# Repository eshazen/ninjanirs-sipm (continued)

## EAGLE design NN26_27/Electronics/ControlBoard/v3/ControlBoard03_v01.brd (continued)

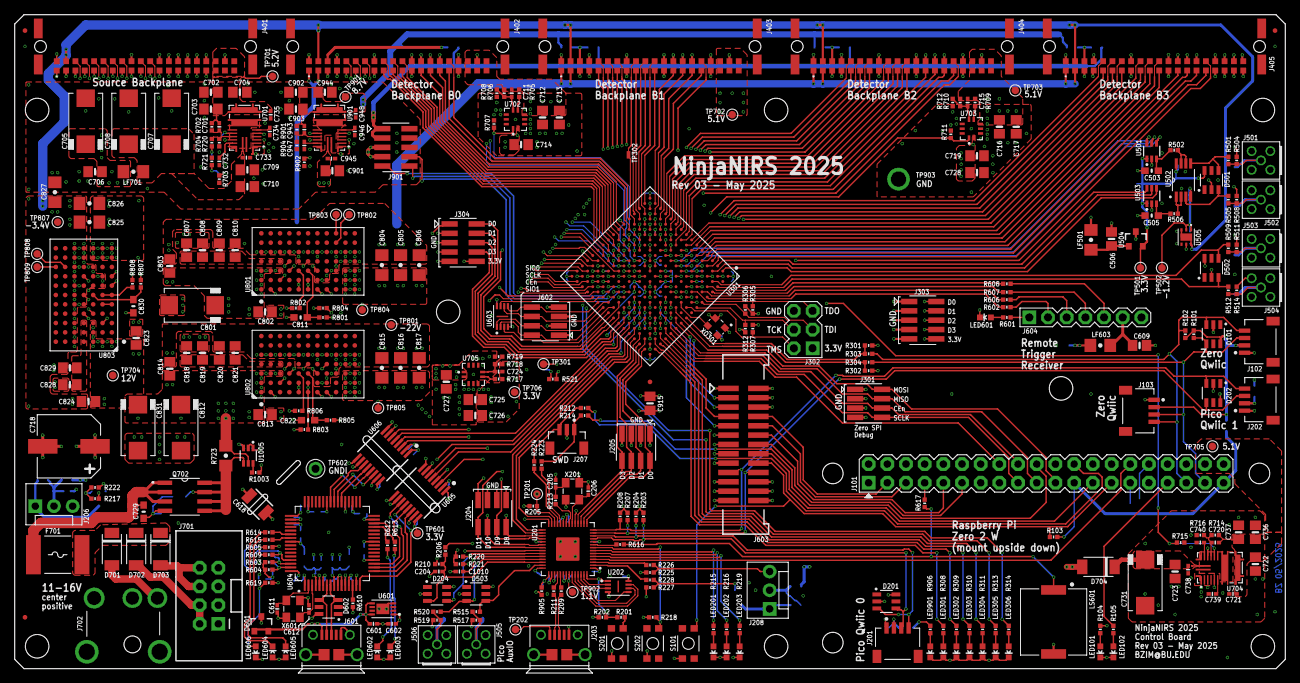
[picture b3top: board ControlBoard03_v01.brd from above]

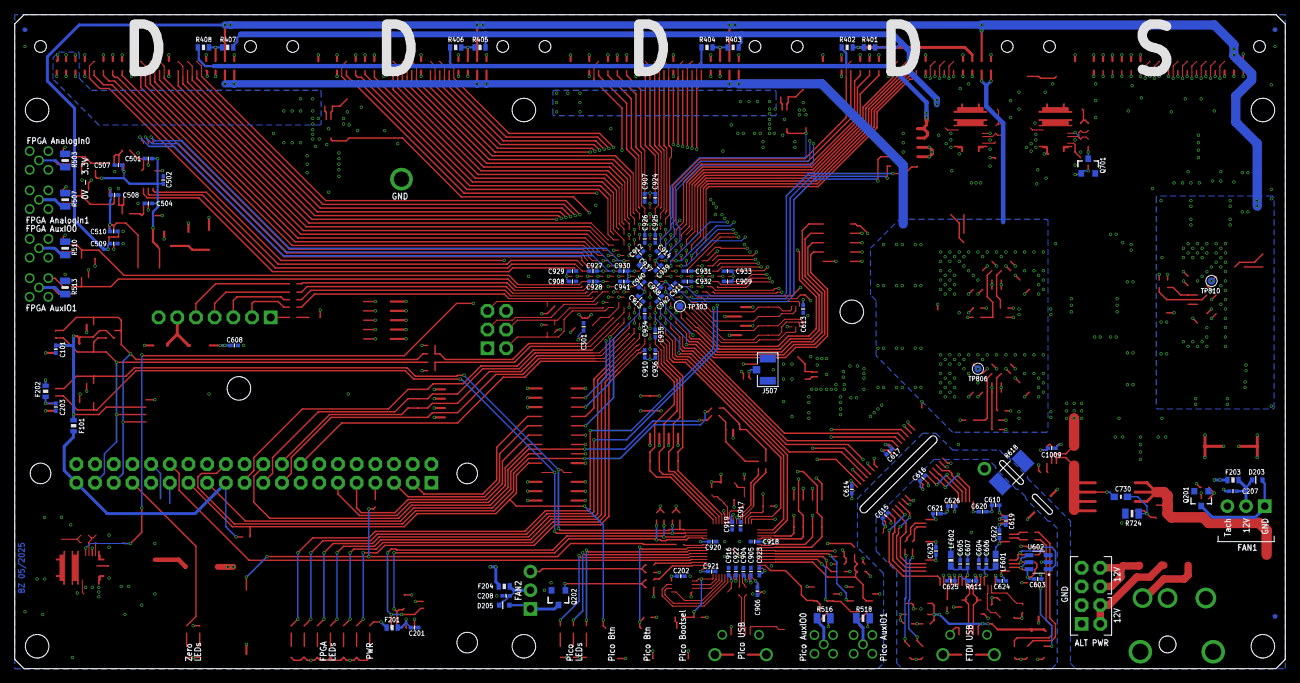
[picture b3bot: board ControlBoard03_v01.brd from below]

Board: 6 copper layers, 172.7 x 88.9 mm, 445 parts (111 on the bottom side), 379 nets.

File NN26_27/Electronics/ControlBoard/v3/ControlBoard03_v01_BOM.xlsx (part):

Designator | Value | Footprint | Populate | MPN | Manufacturer | MPN | Manufacturer
C1009 | 0.1u | 0402-CAP | 1 | GRM155R71H104KE14D | Murata
C101 | 0.1u | 0402-CAP | 1 | GRM155R71H104KE14D | Murata
C1010 | 0.1u | 0402-CAP | 1 | GRM155R71H104KE14D | Murata
C201 | 0.1u | 0402-CAP | 1 | GRM155R71H104KE14D | Murata
C202 | 0.1u | 0402-CAP | 1 | GRM155R71H104KE14D | Murata
C203 | 0.1u | 0402-CAP | 1 | GRM155R71H104KE14D | Murata
C204 | 0.1u | 0402-CAP | 1 | GRM155R71H104KE14D | Murata
C205 | 27p | 0402-CAP | 1 | GCM1555C1H270JA16D | Murata
C206 | 27p | 0402-CAP | 1 | GCM1555C1H270JA16D | Murata
C207 | 0.1u | 0402-CAP | 1 | GRM155R71H104KE14D | Murata
C208 | 0.1u | 0402-CAP | 1 | GRM155R71H104KE14D | Murata
C301 | 0.1u | 0402-CAP | 1 | GRM155R71H104KE14D | Murata
C501 | 0.1u | 0402-CAP | 1 | GRM155R71H104KE14D | Murata
C502 | 4.7u | 0402-CAP | 1 | CL05A475MP5NRNC | Samsung Electro-Mechanics
C503 | 10n | 0603-CAP | 1 | GRM1885C1H103JA01D | Murata
C504 | 0.1u | 0402-CAP | 1 | GRM155R71H104KE14D | Murata
C505 | 10n | 0603-CAP | 1 | GRM1885C1H103JA01D | Murata
C506 | 22u | 0805-CAP | 1 | CL21A226MAYNNNE | Samsung Electro-Mechanics
C507 | 0.1u | 0402-CAP | 1 | GRM155R71H104KE14D | Murata
C508 | 0.1u | 0402-CAP | 1 | GRM155R71H104KE14D | Murata
C509 | 4.7u | 0402-CAP | 1 | CL05A475MP5NRNC | Samsung Electro-Mechanics
C510 | 4.7u | 0402-CAP | 1 | CL05A475MP5NRNC | Samsung Electro-Mechanics
C601 | 4.7u | 0402-CAP | 1 | CL05A475MP5NRNC | Samsung Electro-Mechanics
C602 | 4.7u | 0402-CAP | 1 | CL05A475MP5NRNC | Samsung Electro-Mechanics
C603 | 0.1u | 0402-CAP | 1 | GRM155R71H104KE14D | Murata
C604 | 4.7u | 0402-CAP | 1 | CL05A475MP5NRNC | Samsung Electro-Mechanics
C605 | 4.7u | 0402-CAP | 1 | CL05A475MP5NRNC | Samsung Electro-Mechanics
C606 | 0.1u | 0402-CAP | 1 | GRM155R71H104KE14D | Murata
C607 | 0.1u | 0402-CAP | 1 | GRM155R71H104KE14D | Murata
C608 | 0.1u | 0402-CAP | 1 | GRM155R71H104KE14D | Murata
C609 | 22u | 0805-CAP | 1 | CL21A226MAYNNNE | Samsung Electro-Mechanics
C610 | 4.7u | 0402-CAP | 1 | CL05A475MP5NRNC | Samsung Electro-Mechanics
C611 | 27p | 0402-CAP | 1 | GCM1555C1H270JA16D | Murata
C612 | 27p | 0402-CAP | 1 | GCM1555C1H270JA16D | Murata
C613 | 0.1u | 0402-CAP | 1 | GRM155R71H104KE14D | Murata
C614 | 0.1u | 0402-CAP | 1 | GRM155R71H104KE14D | Murata
C615 | 0.1u | 0402-CAP | 1 | GRM155R71H104KE14D | Murata
C616 | 0.1u | 0402-CAP | 1 | GRM155R71H104KE14D | Murata
C617 | 0.1u | 0402-CAP | 1 | GRM155R71H104KE14D | Murata
C618 | DNP | 1210 | 0
C619 | 0.1u | 0402-CAP | 1 | GRM155R71H104KE14D | Murata
C620 | 0.1u | 0402-CAP | 1 | GRM155R71H104KE14D | Murata
C621 | 0.1u | 0402-CAP | 1 | GRM155R71H104KE14D | Murata
C622 | 0.1u | 0402-CAP | 1 | GRM155R71H104KE14D | Murata
C623 | 0.1u | 0402-CAP | 1 | GRM155R71H104KE14D | Murata
C624 | 0.1u | 0402-CAP | 1 | GRM155R71H104KE14D | Murata
C625 | 0.1u | 0402-CAP | 1 | GRM155R71H104KE14D | Murata
C626 | 0.1u | 0402-CAP | 1 | GRM155R71H104KE14D | Murata
C701 | 39p | 0402-CAP | 1 | GCM1555C1H390JA16D | Murata
C702 | 22u | 0805-CAP | 1 | CL21A226MAYNNNE | Samsung Electro-Mechanics
C703 | 22u | 0805-CAP | 1 | CL21A226MAYNNNE | Samsung Electro-Mechanics
C704 | 22u | 0805-CAP | 1 | CL21A226MAYNNNE | Samsung Electro-Mechanics
C705 | 100u/25V | 2917-CAP | 1 | TCJD107M025R0055 | KYOCERA AVX | 25TQC100MD3 | Panasonic
C706 | 22u | 0805-CAP | 1 | CL21A226MAYNNNE | Samsung Electro-Mechanics
C707 | 100u/25V | 2917-CAP | 1 | TCJD107M025R0055 | KYOCERA AVX | 25TQC100MD3 | Panasonic
C708 | 100u/25V | 2917-CAP | 1 | TCJD107M025R0055 | KYOCERA AVX | 25TQC100MD3 | Panasonic
C709 | 22u | 0805-CAP | 1 | CL21A226MAYNNNE | Samsung Electro-Mechanics
C710 | 22u | 0805-CAP | 1 | CL21A226MAYNNNE | Samsung Electro-Mechanics
C711 | 39p | 0402-CAP | 1 | GCM1555C1H390JA16D | Murata
C712 | 22u | 0805-CAP | 1 | CL21A226MAYNNNE | Samsung Electro-Mechanics
C713 | 22u | 0805-CAP | 1 | CL21A226MAYNNNE | Samsung Electro-Mechanics
C714 | 22u | 0805-CAP | 1 | CL21A226MAYNNNE | Samsung Electro-Mechanics
C715 | 39p | 0402-CAP | 1 | GCM1555C1H390JA16D | Murata
C716 | 22u | 0805-CAP | 1 | CL21A226MAYNNNE | Samsung Electro-Mechanics
C717 | 22u | 0805-CAP | 1 | CL21A226MAYNNNE | Samsung Electro-Mechanics
C718 | 330u/25V | CAP-SMD-POL-8X10 | 1 | EEE-FP1E331AP | Panasonic
C719 | 22u | 0805-CAP | 1 | CL21A226MAYNNNE | Samsung Electro-Mechanics
C720 | 39p | 0402-CAP | 1 | GCM1555C1H390JA16D | Murata
C721 | 0.1u | 0402-CAP | 1 | GRM155R71H104KE14D | Murata
C722 | 22u | 0805-CAP | 1 | CL21A226MAYNNNE | Samsung Electro-Mechanics
C723 | 22u | 0805-CAP | 1 | CL21A226MAYNNNE | Samsung Electro-Mechanics
C724 | 39p | 0402-CAP | 1 | GCM1555C1H390JA16D | Murata
C725 | 22u | 0805-CAP | 1 | CL21A226MAYNNNE | Samsung Electro-Mechanics
C726 | 22u | 0805-CAP | 1 | CL21A226MAYNNNE | Samsung Electro-Mechanics
C727 | 22u | 0805-CAP | 1 | CL21A226MAYNNNE | Samsung Electro-Mechanics
C728 | 22u | 0805-CAP | 1 | CL21A226MAYNNNE | Samsung Electro-Mechanics
C729 | 10n | 0603-CAP | 1 | GRM1885C1H103JA01D | Murata
C730 | 1n | 0603-CAP | 1 | GRM1885C1H102JA01D | Murata
C731 | 100u/25V | 2917-CAP | 1 | TCJD107M025R0055 | KYOCERA AVX | 25TQC100MD3 | Panasonic
C732 | 0.1u | 0402-CAP | 1 | GRM155R71H104KE14D | Murata
C733 | 0.1u | 0402-CAP | 1 | GRM155R71H104KE14D | Murata
C734 | DNP | 0402-CAP | 0
C735 | 0.1u | 0402-CAP | 1 | GRM155R71H104KE14D | Murata
C736 | 22u | 0805-CAP | 1 | CL21A226MAYNNNE | Samsung Electro-Mechanics
C737 | 22u | 0805-CAP | 1 | CL21A226MAYNNNE | Samsung Electro-Mechanics
C738 | 0.1u | 0402-CAP | 1 | GRM155R71H104KE14D | Murata
C739 | DNP | 0402-CAP | 0
C740 | 0.1u | 0402-CAP | 1 | GRM155R71H104KE14D | Murata
C801 | 100u/25V | 2917-CAP | 1 | TCJD107M025R0055 | KYOCERA AVX | 25TQC100MD3 | Panasonic
C802 | 4.7u | 0805-CAP | 1 | CL21A475KBQNNNE | Samsung Electro-Mechanics
C803 | 4.7u | 0805-CAP | 1 | CL21A475KBQNNNE | Samsung Electro-Mechanics
C804 | 10u | 1206 | 1 | CL31A106MBHNNNE | Samsung Electro-Mechanics
C805 | 10u | 1206 | 1 | CL31A106MBHNNNE | Samsung Electro-Mechanics
C806 | 10u | 1206 | 1 | CL31A106MBHNNNE | Samsung Electro-Mechanics
C807 | 4.7u | 0805-CAP | 1 | CL21A475KBQNNNE | Samsung Electro-Mechanics
C808 | 4.7u | 0805-CAP | 1 | CL21A475KBQNNNE | Samsung Electro-Mechanics
C809 | 4.7u | 0805-CAP | 1 | CL21A475KBQNNNE | Samsung Electro-Mechanics
C810 | 4.7u | 0805-CAP | 1 | CL21A475KBQNNNE | Samsung Electro-Mechanics
C811 | 1u | 0603-CAP | 1 | CL10A105KB8NNNC | Samsung Electro-Mechanics
C812 | 100u/25V | 2917-CAP | 1 | TCJD107M025R0055 | KYOCERA AVX | 25TQC100MD3 | Panasonic
C813 | 4.7u | 0805-CAP | 1 | CL21A475KBQNNNE | Samsung Electro-Mechanics
C814 | 4.7u | 0805-CAP | 1 | CL21A475KBQNNNE | Samsung Electro-Mechanics
C815 | 10u | 1206 | 1 | CL31A106MBHNNNE | Samsung Electro-Mechanics
C816 | 10u | 1206 | 1 | CL31A106MBHNNNE | Samsung Electro-Mechanics
C817 | 10u | 1206 | 1 | CL31A106MBHNNNE | Samsung Electro-Mechanics
C818 | 4.7u | 0805-CAP | 1 | CL21A475KBQNNNE | Samsung Electro-Mechanics
C819 | 4.7u | 0805-CAP | 1 | CL21A475KBQNNNE | Samsung Electro-Mechanics
C820 | 4.7u | 0805-CAP | 1 | CL21A475KBQNNNE | Samsung Electro-Mechanics
C821 | 4.7u | 0805-CAP | 1 | CL21A475KBQNNNE | Samsung Electro-Mechanics
C822 | 1u | 0603-CAP | 1 | CL10A105KB8NNNC | Samsung Electro-Mechanics
C823 | 4.7u | 0805-CAP | 1 | CL21A475KBQNNNE | Samsung Electro-Mechanics
C824 | 4.7u | 0805-CAP | 1 | CL21A475KBQNNNE | Samsung Electro-Mechanics
C825 | 100u | 1206 | 1 | CL31A107MQHNNNE | Samsung Electro-Mechanics
C826 | 100u | 1206 | 1 | CL31A107MQHNNNE | Samsung Electro-Mechanics
C827 | DNP | 1206 | 0
C828 | 4.7u | 0805-CAP | 1 | CL21A475KBQNNNE | Samsung Electro-Mechanics
C829 | 4.7u | 0805-CAP | 1 | CL21A475KBQNNNE | Samsung Electro-Mechanics
C830 | 1u | 0603-CAP | 1 | CL10A105KB8NNNC | Samsung Electro-Mechanics
C831 | 100u/25V | 2917-CAP | 1 | TCJD107M025R0055 | KYOCERA AVX | 25TQC100MD3 | Panasonic
C901 | 22u | 0805-CAP | 1 | CL21A226MAYNNNE | Samsung Electro-Mechanics
C902 | 22u | 0805-CAP | 1 | CL21A226MAYNNNE | Samsung Electro-Mechanics
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
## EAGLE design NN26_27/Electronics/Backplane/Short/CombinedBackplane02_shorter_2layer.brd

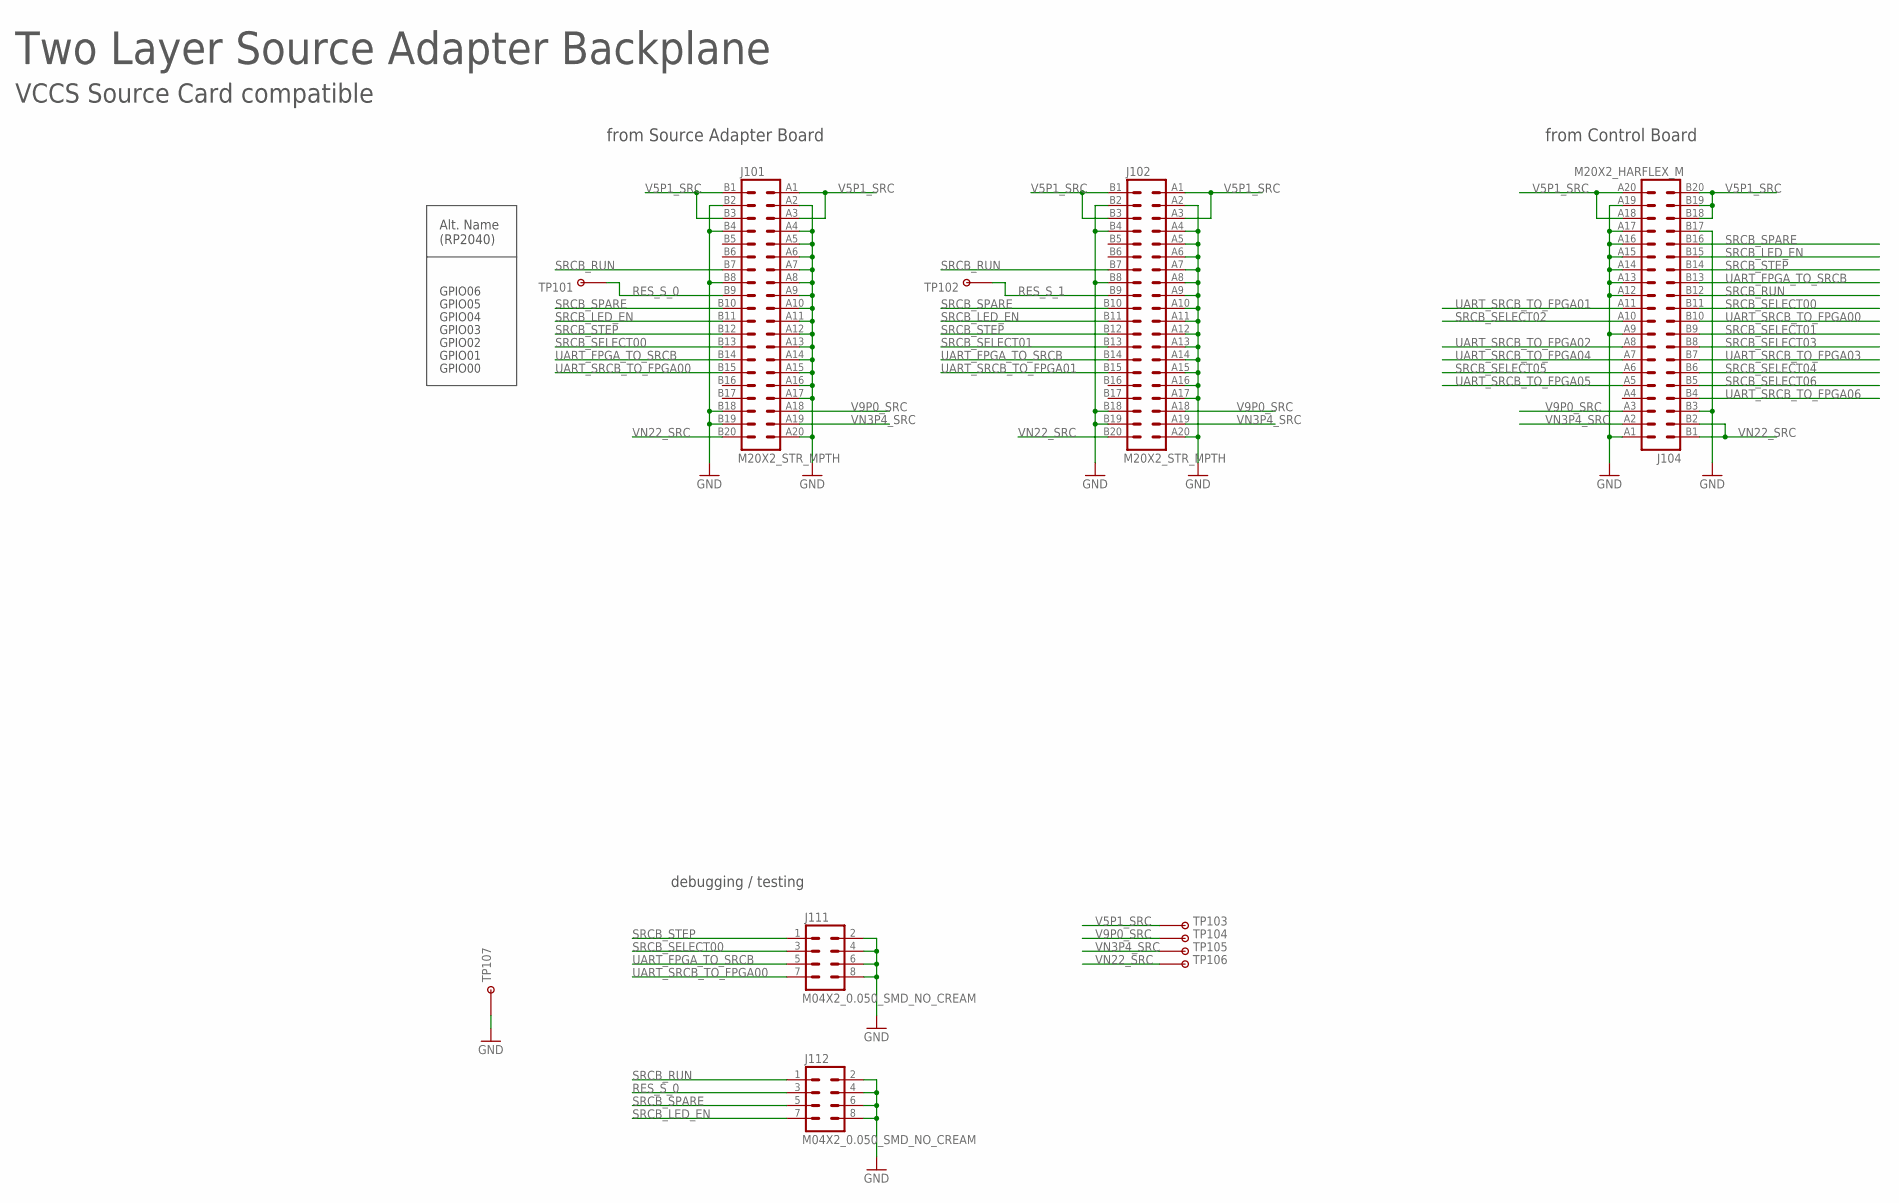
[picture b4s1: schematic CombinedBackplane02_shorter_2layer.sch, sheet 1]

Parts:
J101, J102: M20X2_STR_MPTH; M20X2_HARFLEX_F_STR_MPTH
J104: M20X2_HARFLEX_M
J111, J112: M04X2_0.050_SMD_NO_CREAM
TP101, TP102, TP103, TP104, TP105, TP106: TESTPOINT_ROUND; TESTPAD_ROUND
TP107: TESTPOINT1X01; 1X01

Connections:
GND_SRC: J101.A2 (4), J101.A4 (8), J101.A5 (10), J101.A6 (12), J101.A7 (14), J101.A8 (16), J101.A9 (18), J101.A10 (20), J101.A11 (22), J101.A12 (24), J101.A13 (26), J101.A14 (28), J101.A15 (30), J101.A16 (32), J101.A17 (34), J101.A20 (40), J101.B2 (3), J101.B4 (7), J101.B8 (15), J101.B18 (35), J101.B19 (37), J102.A2 (4), J102.A4 (8), J102.A5 (10), J102.A6 (12), J102.A7 (14), J102.A8 (16), J102.A9 (18), J102.A10 (20), J102.A11 (22), J102.A12 (24), J102.A13 (26), J102.A14 (28), J102.A15 (30), J102.A16 (32), J102.A17 (34), J102.A20 (40), J102.B2 (3), J102.B4 (7), J102.B8 (15), J102.B18 (35), J102.B19 (37), J104.A1 (2), J104.A9 (18), J104.A12 (24), J104.A13 (26), J104.A14 (28), J104.A15 (30), J104.A16 (32), J104.A17 (34), J104.A19 (38), J104.B3 (5), J104.B17 (33), J111.2, J111.4, J111.6, J111.8, J112.2, J112.4, J112.6, J112.8, TP107.1
RES_S_0: J101.B9 (17), J112.3, TP101.P$1
RES_S_1: J102.B9 (17), TP102.P$1
SRCB_LED_EN: J101.B11 (21), J102.B11 (21), J104.B15 (29), J112.7
SRCB_RUN: J101.B7 (13), J102.B7 (13), J104.B12 (23), J112.1
SRCB_SELECT00: J101.B13 (25), J104.B11 (21), J111.3
SRCB_SELECT01: J102.B13 (25), J104.B9 (17)
SRCB_SELECT02: J104.A10 (20)
SRCB_SELECT03: J104.B8 (15)
SRCB_SELECT04: J104.B6 (11)
SRCB_SELECT05: J104.A6 (12)
SRCB_SELECT06: J104.B5 (9)
SRCB_SPARE: J101.B10 (19), J102.B10 (19), J104.B16 (31), J112.5
SRCB_STEP: J101.B12 (23), J102.B12 (23), J104.B14 (27), J111.1
UART_FPGA_TO_SRCB: J101.B14 (27), J102.B14 (27), J104.B13 (25), J111.5
UART_SRCB_TO_FPGA00: J101.B15 (29), J104.B10 (19), J111.7
UART_SRCB_TO_FPGA01: J102.B15 (29), J104.A11 (22)
UART_SRCB_TO_FPGA02: J104.A8 (16)
UART_SRCB_TO_FPGA03: J104.B7 (13)
UART_SRCB_TO_FPGA04: J104.A7 (14)
UART_SRCB_TO_FPGA05: J104.A5 (10)
UART_SRCB_TO_FPGA06: J104.B4 (7)
V5P1_SRC: J101.A1 (2), J101.A3 (6), J101.B1 (1), J101.B3 (5), J102.A1 (2), J102.A3 (6), J102.B1 (1), J102.B3 (5), J104.A18 (36), J104.A20 (40), J104.B18 (35), J104.B19 (37), J104.B20 (39), TP103.P$1
V9P0_SRC: J101.A18 (36), J102.A18 (36), J104.A3 (6), TP104.P$1
VN3P4_SRC: J101.A19 (38), J102.A19 (38), J104.A2 (4), TP105.P$1
VN22_SRC: J101.B20 (39), J102.B20 (39), J104.B1 (1), J104.B2 (3), TP106.P$1

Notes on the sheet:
Two Layer Source Adapter Backplane
from Source Adapter Board
from Control Board
GPIO00
GPIO01
GPIO02
GPIO03
GPIO04
GPIO05
GPIO06
debugging / testing
Alt. Name (RP2040)
VCCS Source Card compatible

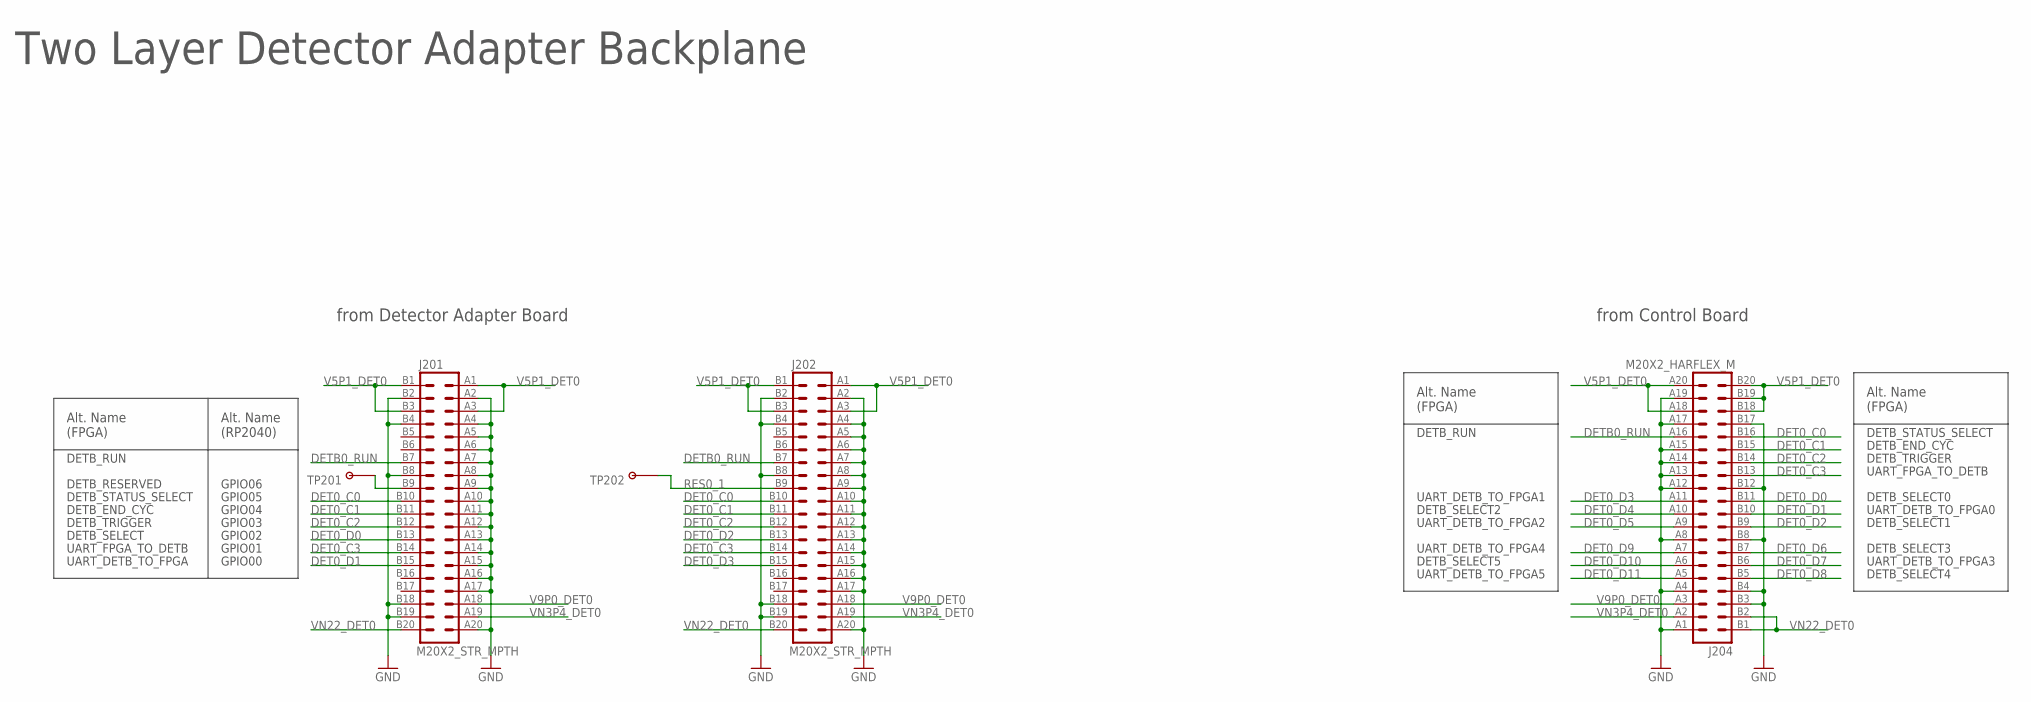
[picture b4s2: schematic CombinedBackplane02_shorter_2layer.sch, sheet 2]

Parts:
J201, J202: M20X2_STR_MPTH; M20X2_HARFLEX_F_STR_MPTH
J204: M20X2_HARFLEX_M
TP201, TP202: TESTPOINT_ROUND; TESTPAD_ROUND

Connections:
DET0_C0: J201.B10 (19), J202.B10 (19), J204.B16 (31)
DET0_C1: J201.B11 (21), J202.B11 (21), J204.B15 (29)
DET0_C2: J201.B12 (23), J202.B12 (23), J204.B14 (27)
DET0_C3: J201.B14 (27), J202.B14 (27), J204.B13 (25)
DET0_D0: J201.B13 (25), J204.B11 (21)
DET0_D1: J201.B15 (29), J204.B10 (19)
DET0_D2: J202.B13 (25), J204.B9 (17)
DET0_D3: J202.B15 (29), J204.A11 (22)
DET0_D4: J204.A10 (20)
DET0_D5: J204.A9 (18)
DET0_D6: J204.B7 (13)
DET0_D7: J204.B6 (11)
DET0_D8: J204.B5 (9)
DET0_D9: J204.A7 (14)
DET0_D10: J204.A6 (12)
DET0_D11: J204.A5 (10)
DETB0_RUN: J201.B7 (13), J202.B7 (13), J204.A16 (32)
GND: J201.A2 (4), J201.A4 (8), J201.A5 (10), J201.A6 (12), J201.A7 (14), J201.A8 (16), J201.A9 (18), J201.A10 (20), J201.A11 (22), J201.A12 (24), J201.A13 (26), J201.A14 (28), J201.A15 (30), J201.A16 (32), J201.A17 (34), J201.A20 (40), J201.B2 (3), J201.B4 (7), J201.B8 (15), J201.B18 (35), J201.B19 (37), J202.A2 (4), J202.A4 (8), J202.A5 (10), J202.A6 (12), J202.A7 (14), J202.A8 (16), J202.A9 (18), J202.A10 (20), J202.A11 (22), J202.A12 (24), J202.A13 (26), J202.A14 (28), J202.A15 (30), J202.A16 (32), J202.A17 (34), J202.A20 (40), J202.B2 (3), J202.B4 (7), J202.B8 (15), J202.B18 (35), J202.B19 (37), J204.A1 (2), J204.A4 (8), J204.A8 (16), J204.A12 (24), J204.A13 (26), J204.A14 (28), J204.A15 (30), J204.A17 (34), J204.A19 (38), J204.B3 (5), J204.B4 (7), J204.B8 (15), J204.B12 (23), J204.B17 (33); also elsewhere on the board
unnamed: J201.B9 (17), TP201.P$1
RES0_1: J202.B9 (17), TP202.P$1
V5P1_DET0: J201.A1 (2), J201.A3 (6), J201.B1 (1), J201.B3 (5), J202.A1 (2), J202.A3 (6), J202.B1 (1), J202.B3 (5), J204.A18 (36), J204.A20 (40), J204.B18 (35), J204.B19 (37), J204.B20 (39)
V9P0_DET0: J201.A18 (36), J202.A18 (36), J204.A3 (6)
VN3P4_DET0: J201.A19 (38), J202.A19 (38), J204.A2 (4)
VN22_DET0: J201.B20 (39), J202.B20 (39), J204.B1 (1), J204.B2 (3)

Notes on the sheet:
Two Layer Detector Adapter Backplane
from Detector Adapter Board
from Control Board
GPIO00
GPIO01
GPIO02
GPIO03
GPIO04
GPIO05
GPIO06
UART_DETB_TO_FPGA
UART_FPGA_TO_DETB
DETB_SELECT
DETB_TRIGGER
DETB_END_CYC
DETB_STATUS_SELECT
DETB_RESERVED
DETB_RUN
UART_DETB_TO_FPGA0
DETB_SELECT0
DETB_SELECT1
DETB_SELECT2
DETB_SELECT5
DETB_SELECT3
DETB_SELECT4
UART_DETB_TO_FPGA1
UART_DETB_TO_FPGA2
UART_DETB_TO_FPGA4
UART_DETB_TO_FPGA5
UART_DETB_TO_FPGA3
Alt. Name (FPGA)
Alt. Name (RP2040)

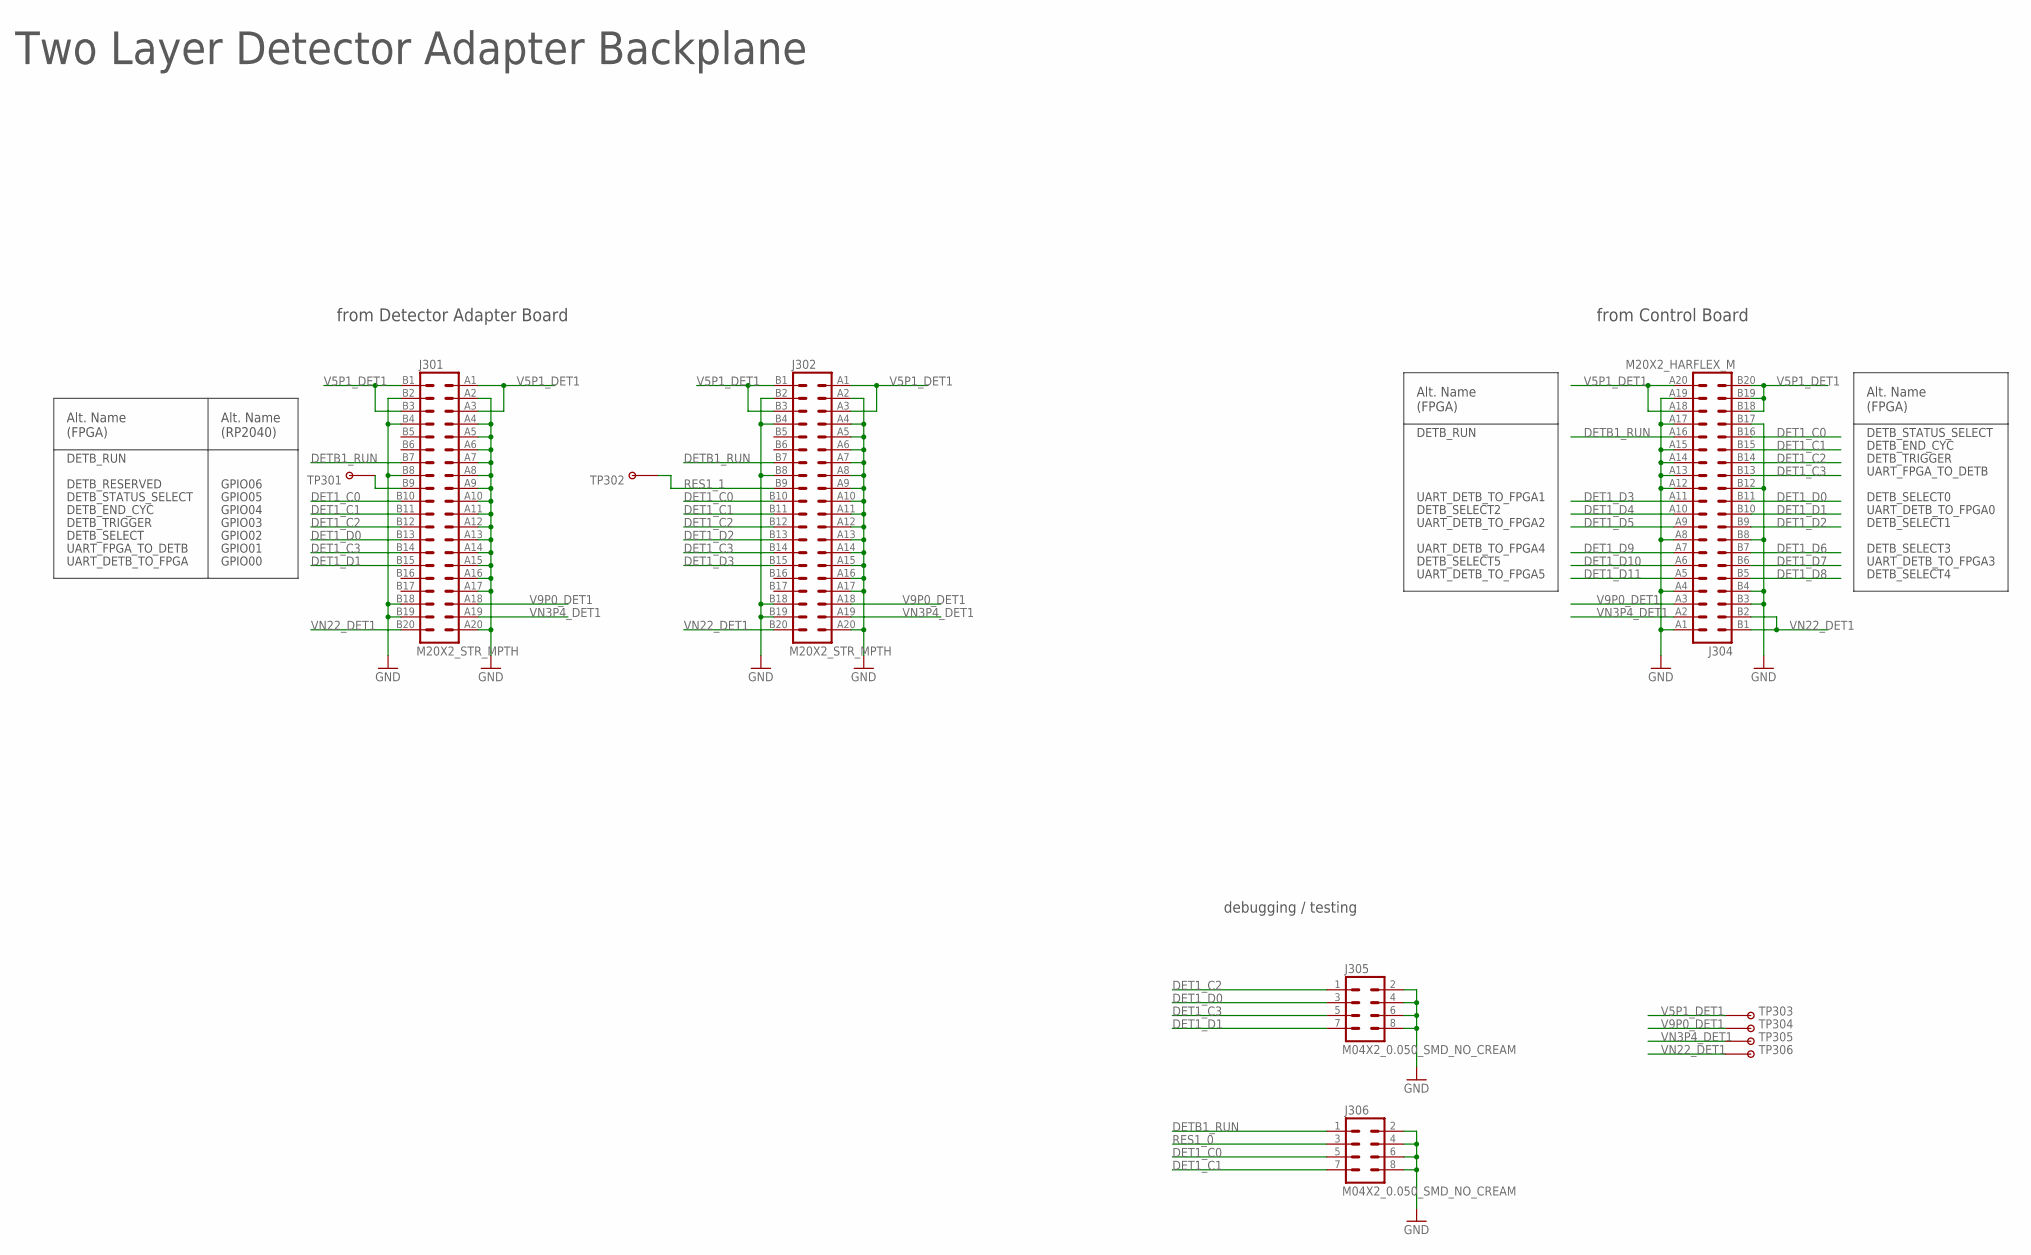
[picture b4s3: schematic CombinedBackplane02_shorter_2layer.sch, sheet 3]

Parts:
J301, J302: M20X2_STR_MPTH; M20X2_HARFLEX_F_STR_MPTH
J304: M20X2_HARFLEX_M
J305, J306: M04X2_0.050_SMD_NO_CREAM
TP301, TP302, TP303, TP304, TP305, TP306: TESTPOINT_ROUND; TESTPAD_ROUND

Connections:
DET1_C0: J301.B10 (19), J302.B10 (19), J304.B16 (31), J306.5
DET1_C1: J301.B11 (21), J302.B11 (21), J304.B15 (29), J306.7
DET1_C2: J301.B12 (23), J302.B12 (23), J304.B14 (27), J305.1
DET1_C3: J301.B14 (27), J302.B14 (27), J304.B13 (25), J305.5
DET1_D0: J301.B13 (25), J304.B11 (21), J305.3
DET1_D1: J301.B15 (29), J304.B10 (19), J305.7
DET1_D2: J302.B13 (25), J304.B9 (17)
DET1_D3: J302.B15 (29), J304.A11 (22)
DET1_D4: J304.A10 (20)
DET1_D5: J304.A9 (18)
DET1_D6: J304.B7 (13)
DET1_D7: J304.B6 (11)
DET1_D8: J304.B5 (9)
DET1_D9: J304.A7 (14)
DET1_D10: J304.A6 (12)
DET1_D11: J304.A5 (10)
DETB1_RUN: J301.B7 (13), J302.B7 (13), J304.A16 (32), J306.1
GND: J301.A2 (4), J301.A4 (8), J301.A5 (10), J301.A6 (12), J301.A7 (14), J301.A8 (16), J301.A9 (18), J301.A10 (20), J301.A11 (22), J301.A12 (24), J301.A13 (26), J301.A14 (28), J301.A15 (30), J301.A16 (32), J301.A17 (34), J301.A20 (40), J301.B2 (3), J301.B4 (7), J301.B8 (15), J301.B18 (35), J301.B19 (37), J302.A2 (4), J302.A4 (8), J302.A5 (10), J302.A6 (12), J302.A7 (14), J302.A8 (16), J302.A9 (18), J302.A10 (20), J302.A11 (22), J302.A12 (24), J302.A13 (26), J302.A14 (28), J302.A15 (30), J302.A16 (32), J302.A17 (34), J302.A20 (40), J302.B2 (3), J302.B4 (7), J302.B8 (15), J302.B18 (35), J302.B19 (37), J304.A1 (2), J304.A4 (8), J304.A8 (16), J304.A12 (24), J304.A13 (26), J304.A14 (28), J304.A15 (30), J304.A17 (34), J304.A19 (38), J304.B3 (5), J304.B4 (7), J304.B8 (15), J304.B12 (23), J304.B17 (33), J305.2, J305.4, J305.6, J305.8, J306.2, J306.4, J306.6, J306.8; also elsewhere on the board
RES1_0: J301.B9 (17), J306.3, TP301.P$1
RES1_1: J302.B9 (17), TP302.P$1
V5P1_DET1: J301.A1 (2), J301.A3 (6), J301.B1 (1), J301.B3 (5), J302.A1 (2), J302.A3 (6), J302.B1 (1), J302.B3 (5), J304.A18 (36), J304.A20 (40), J304.B18 (35), J304.B19 (37), J304.B20 (39), TP303.P$1
V9P0_DET1: J301.A18 (36), J302.A18 (36), J304.A3 (6), TP304.P$1
VN3P4_DET1: J301.A19 (38), J302.A19 (38), J304.A2 (4), TP305.P$1
VN22_DET1: J301.B20 (39), J302.B20 (39), J304.B1 (1), J304.B2 (3), TP306.P$1

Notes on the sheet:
Two Layer Detector Adapter Backplane
from Detector Adapter Board
from Control Board
GPIO00
GPIO01
GPIO02
GPIO03
GPIO04
GPIO05
GPIO06
UART_DETB_TO_FPGA
UART_FPGA_TO_DETB
DETB_SELECT
DETB_TRIGGER
DETB_END_CYC
DETB_STATUS_SELECT
DETB_RESERVED
DETB_RUN
debugging / testing
UART_DETB_TO_FPGA0
DETB_SELECT0
DETB_SELECT1
DETB_SELECT2
DETB_SELECT5
DETB_SELECT3
DETB_SELECT4
UART_DETB_TO_FPGA1
UART_DETB_TO_FPGA2
UART_DETB_TO_FPGA4
UART_DETB_TO_FPGA5
UART_DETB_TO_FPGA3
Alt. Name (FPGA)
Alt. Name (RP2040)

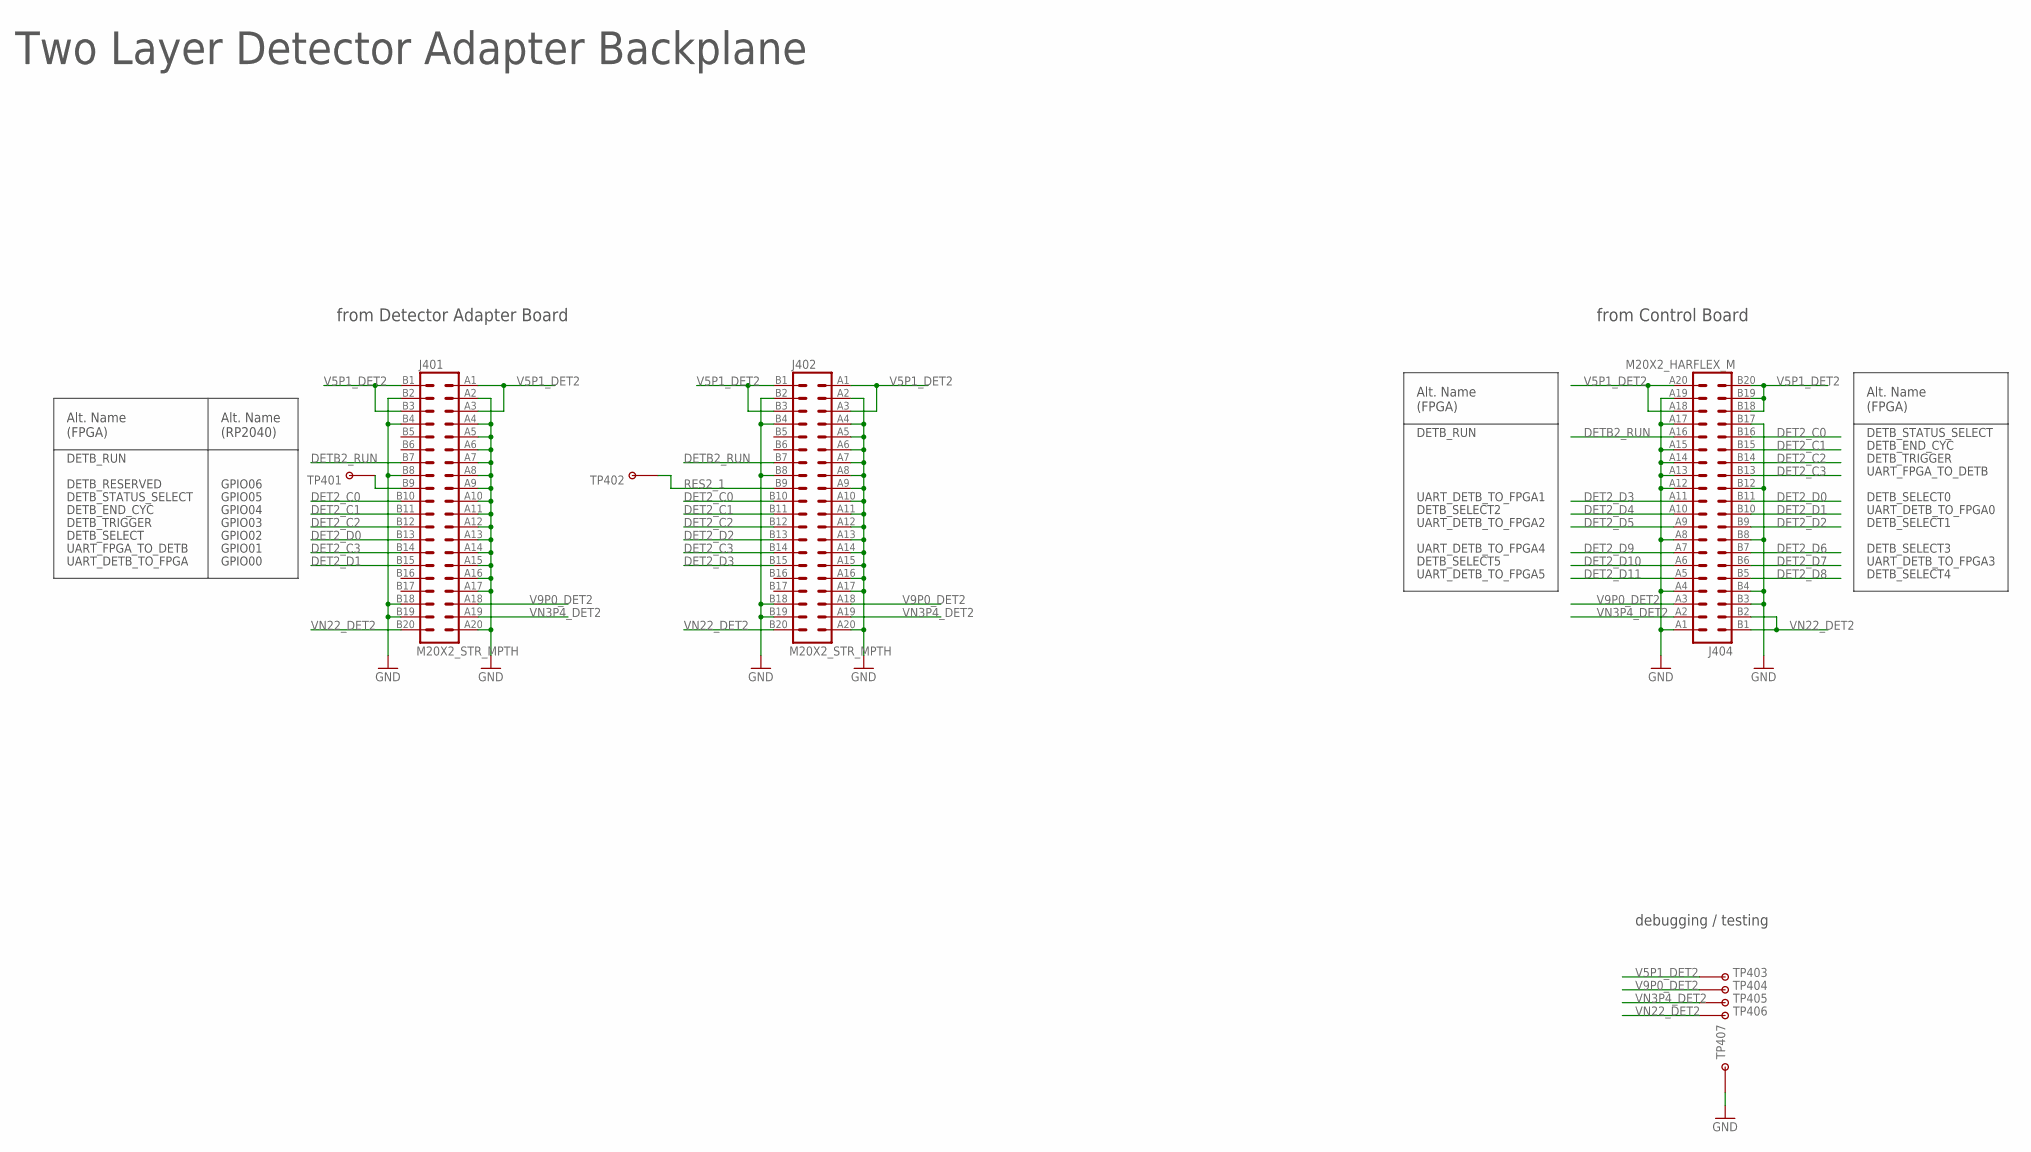
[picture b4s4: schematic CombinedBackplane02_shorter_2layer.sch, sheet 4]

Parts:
J401, J402: M20X2_STR_MPTH; M20X2_HARFLEX_F_STR_MPTH
J404: M20X2_HARFLEX_M
TP401, TP402, TP403, TP404, TP405, TP406: TESTPOINT_ROUND; TESTPAD_ROUND
TP407: TESTPOINT1X01; 1X01

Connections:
DET2_C0: J401.B10 (19), J402.B10 (19), J404.B16 (31)
DET2_C1: J401.B11 (21), J402.B11 (21), J404.B15 (29)
DET2_C2: J401.B12 (23), J402.B12 (23), J404.B14 (27)
DET2_C3: J401.B14 (27), J402.B14 (27), J404.B13 (25)
DET2_D0: J401.B13 (25), J404.B11 (21)
DET2_D1: J401.B15 (29), J404.B10 (19)
DET2_D2: J402.B13 (25), J404.B9 (17)
DET2_D3: J402.B15 (29), J404.A11 (22)
DET2_D4: J404.A10 (20)
DET2_D5: J404.A9 (18)
DET2_D6: J404.B7 (13)
DET2_D7: J404.B6 (11)
DET2_D8: J404.B5 (9)
DET2_D9: J404.A7 (14)
DET2_D10: J404.A6 (12)
DET2_D11: J404.A5 (10)
DETB2_RUN: J401.B7 (13), J402.B7 (13), J404.A16 (32)
GND: J401.A2 (4), J401.A4 (8), J401.A5 (10), J401.A6 (12), J401.A7 (14), J401.A8 (16), J401.A9 (18), J401.A10 (20), J401.A11 (22), J401.A12 (24), J401.A13 (26), J401.A14 (28), J401.A15 (30), J401.A16 (32), J401.A17 (34), J401.A20 (40), J401.B2 (3), J401.B4 (7), J401.B8 (15), J401.B18 (35), J401.B19 (37), J402.A2 (4), J402.A4 (8), J402.A5 (10), J402.A6 (12), J402.A7 (14), J402.A8 (16), J402.A9 (18), J402.A10 (20), J402.A11 (22), J402.A12 (24), J402.A13 (26), J402.A14 (28), J402.A15 (30), J402.A16 (32), J402.A17 (34), J402.A20 (40), J402.B2 (3), J402.B4 (7), J402.B8 (15), J402.B18 (35), J402.B19 (37), J404.A1 (2), J404.A4 (8), J404.A8 (16), J404.A12 (24), J404.A13 (26), J404.A14 (28), J404.A15 (30), J404.A17 (34), J404.A19 (38), J404.B3 (5), J404.B4 (7), J404.B8 (15), J404.B12 (23), J404.B17 (33), TP407.1; also elsewhere on the board
RES2_0: J401.B9 (17), TP401.P$1
RES2_1: J402.B9 (17), TP402.P$1
V5P1_DET2: J401.A1 (2), J401.A3 (6), J401.B1 (1), J401.B3 (5), J402.A1 (2), J402.A3 (6), J402.B1 (1), J402.B3 (5), J404.A18 (36), J404.A20 (40), J404.B18 (35), J404.B19 (37), J404.B20 (39), TP403.P$1
V9P0_DET2: J401.A18 (36), J402.A18 (36), J404.A3 (6), TP404.P$1
VN3P4_DET2: J401.A19 (38), J402.A19 (38), J404.A2 (4), TP405.P$1
VN22_DET2: J401.B20 (39), J402.B20 (39), J404.B1 (1), J404.B2 (3), TP406.P$1

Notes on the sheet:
Two Layer Detector Adapter Backplane
from Detector Adapter Board
from Control Board
GPIO00
GPIO01
GPIO02
GPIO03
GPIO04
GPIO05
GPIO06
UART_DETB_TO_FPGA
UART_FPGA_TO_DETB
DETB_SELECT
DETB_TRIGGER
DETB_END_CYC
DETB_STATUS_SELECT
DETB_RESERVED
DETB_RUN
debugging / testing
UART_DETB_TO_FPGA0
DETB_SELECT0
DETB_SELECT1
DETB_SELECT2
DETB_SELECT5
DETB_SELECT3
DETB_SELECT4
UART_DETB_TO_FPGA1
UART_DETB_TO_FPGA2
UART_DETB_TO_FPGA4
UART_DETB_TO_FPGA5
UART_DETB_TO_FPGA3
Alt. Name (FPGA)
Alt. Name (RP2040)

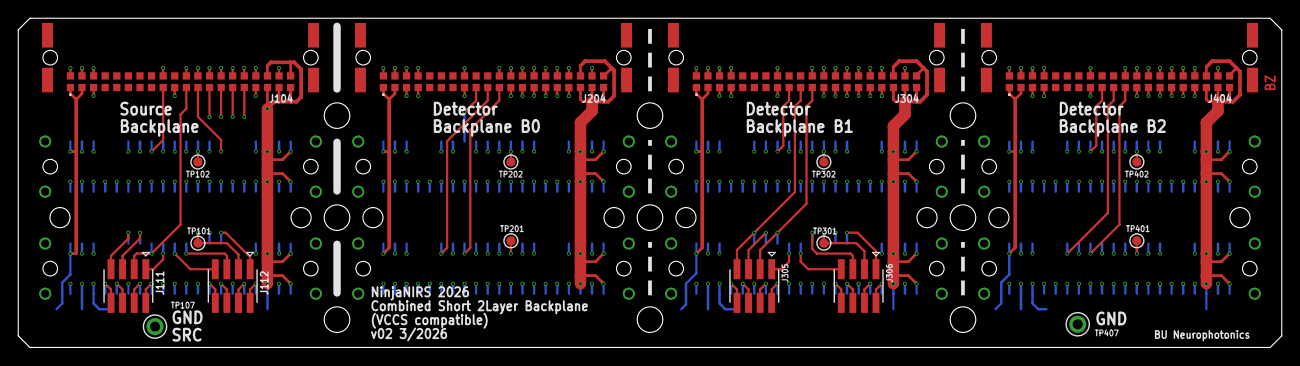
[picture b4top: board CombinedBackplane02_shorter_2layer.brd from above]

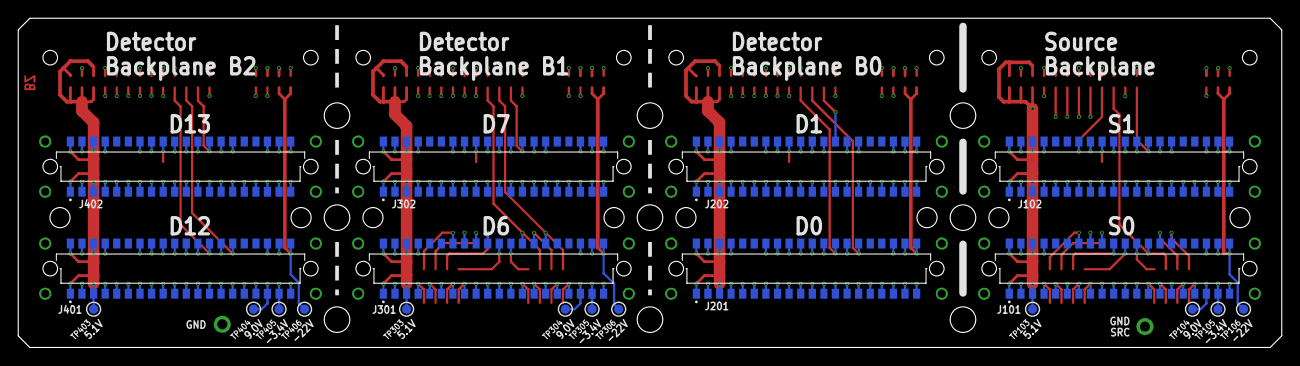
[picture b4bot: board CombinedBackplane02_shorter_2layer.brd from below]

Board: 4 copper layers, 138.4 x 36.1 mm, 38 parts (20 on the bottom side), 62 nets.

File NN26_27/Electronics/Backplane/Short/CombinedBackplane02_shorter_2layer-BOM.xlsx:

CombinedBackplane02_short_2layer |  |  | bzim@bu.edu
Designator | Qty | MPN | Manufacturer | Value | Device | Package
J111, J112, J305, J306 | 4 | DNP |  | M04X2_0.050_SMD_NO_CREAM | M04X2_0.050_SMD_NO_CREAM | M04X2_0.050_SMD_NO_CREAM
J104, J204, J304, J404 | 4 | 1377302 | Phoenix Contact | M20X2_HARFLEX_M | M20X2_HARFLEX_M | M20X2_HARFLEX_M
J101, J102, J201, J202, J301, J302, J401, J402 | 8 | M55-6064042R | Harwin | M20X2_STR_MPTH | M20X2_STR_MPTH | M20X2_HARFLEX_F_STR_MPTH
TP107, TP407 | 2 | DNP |  | TESTPOINT1X01 | TESTPOINT1X01 | 1X01
TP101, TP102, TP103, TP104, TP105, TP106, TP201, TP202, TP301, TP302, TP303, TP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 | 20 | DNP |  | TESTPOINT_ROUND | TESTPOINT_ROUND | TESTPAD_ROUND
